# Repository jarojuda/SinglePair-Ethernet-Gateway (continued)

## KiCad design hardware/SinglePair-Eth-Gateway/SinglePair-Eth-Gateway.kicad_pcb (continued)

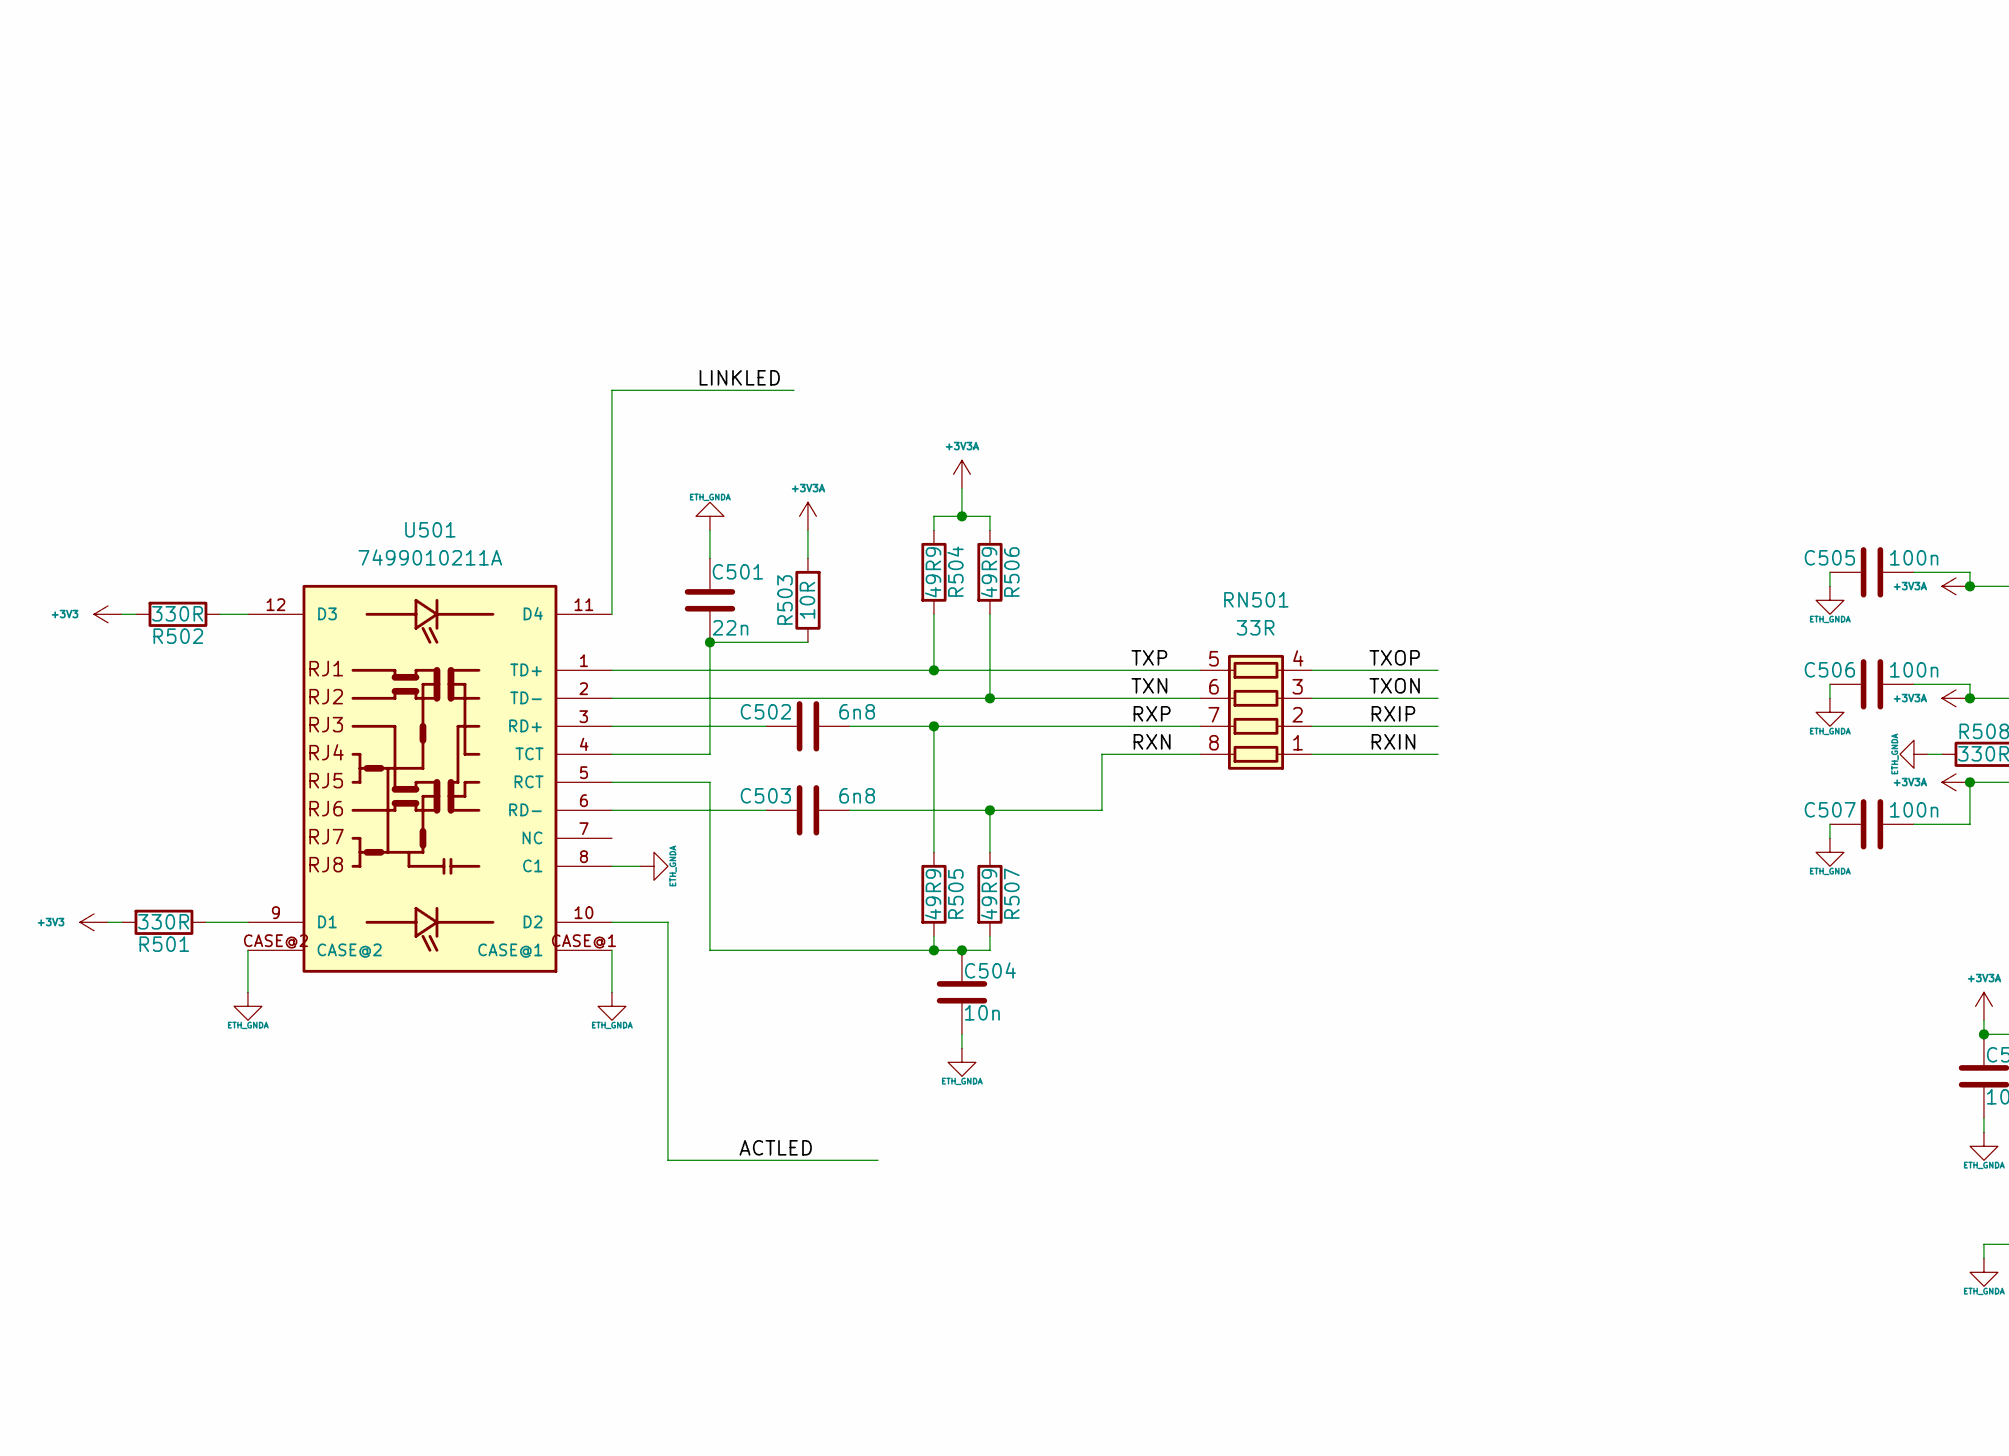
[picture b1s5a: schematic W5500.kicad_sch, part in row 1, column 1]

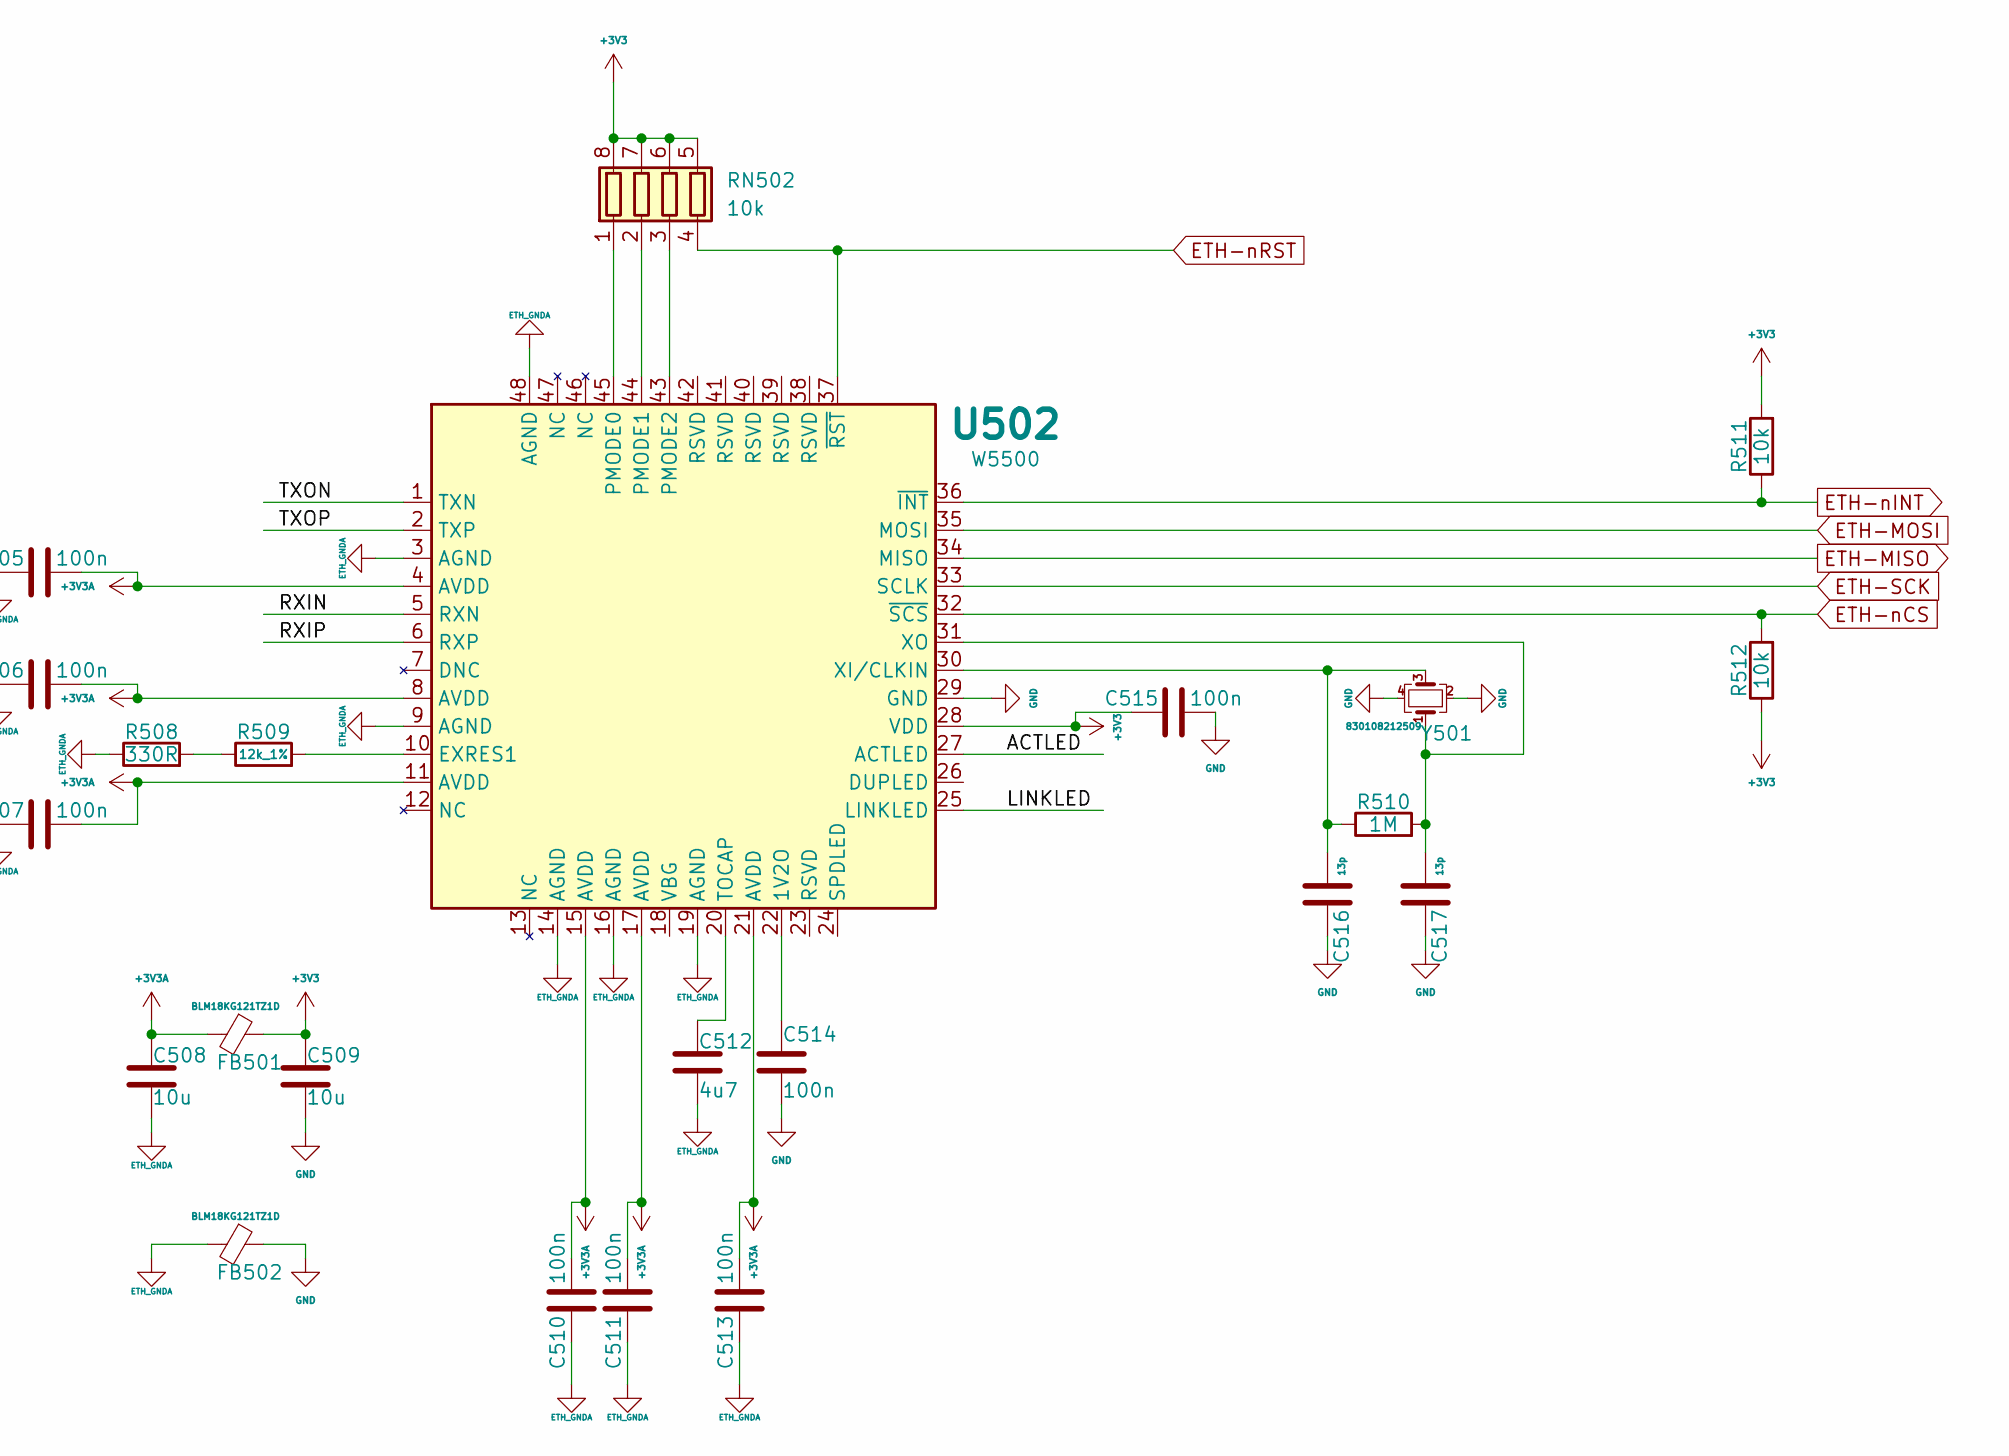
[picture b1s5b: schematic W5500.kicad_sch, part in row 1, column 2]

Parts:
C501: 22n; C_0603_1608Metric
C502, C503: 6n8; C_0603_1608Metric
C504: 10n; C_0603_1608Metric
C505, C506, C507, C510, C511, C513, C514, C515: 100n; C_0603_1608Metric
C508, C509: 10u; C_0805_2012Metric
C512: 4u7; C_0603_1608Metric
C516, C517: 13p; C_0603_1608Metric
FB501, FB502: BLM18KG121TZ1D; FB_0603_1608Metric
R501, R502, R508: 330R; R_0603_1608Metric
R503: 10R; R_0603_1608Metric
R504, R505, R506, R507: 49R9; R_0603_1608Metric
R509: 12k_1%; R_0603_1608Metric
R510: 1M; R_0603_1608Metric
R511, R512: 10k; R_0603_1608Metric
RN501: 33R; R_Array_Concave_4x0603
RN502: 10k; R_Array_Concave_4x0603
U501: 7499010211A
U502: W5500; LQFP-48_7x7mm_P0.5mm
Y501: 830108212509; Crystal_SMD_2016-4Pin_2.0x1.6mm

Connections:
+3V3: C509.1, C515.1, FB501.1, R501.2, R502.2, R511.2, R512.1, RN502.5 (R4.2), RN502.6 (R3.2), RN502.7 (R2.2), RN502.8 (R1.2), U502.28 (VDD); also elsewhere on the board
+3V3A: C505.2, C506.2, C507.2, C508.1, C510.2, C511.2, C513.2, FB501.2, R503.2, R504.1, R506.1, U502.4 (AVDD), U502.8 (AVDD), U502.11 (AVDD), U502.15 (AVDD), U502.17 (AVDD), U502.21 (AVDD)
/Wiznet-W5500/ACTLED: U501.10 (D2), U502.27 (ACTLED)
/Wiznet-W5500/LINKLED: U501.11 (D4), U502.25 (LINKLED)
/Wiznet-W5500/RXIN: RN501.1 (R1.1), U502.5 (RXN)
/Wiznet-W5500/RXIP: RN501.2 (R2.1), U502.6 (RXP)
/Wiznet-W5500/RXN: C503.2, R507.1, RN501.8 (R1.2)
/Wiznet-W5500/RXP: C502.2, R505.1, RN501.7 (R2.2)
/Wiznet-W5500/TXN: R506.2, RN501.6 (R3.2), U501.2 (TD-)
/Wiznet-W5500/TXON: RN501.3 (R3.1), U502.1 (TXN)
/Wiznet-W5500/TXOP: RN501.4 (R4.1), U502.2 (TXP)
/Wiznet-W5500/TXP: R504.2, RN501.5 (R4.2), U501.1 (TD+)
ETH-MISO: U502.34 (MISO); also elsewhere on the board
ETH-MOSI: U502.35 (MOSI); also elsewhere on the board
ETH-SCK: U502.33 (SCLK); also elsewhere on the board
ETH-nCS: R512.2, U502.32 (~SCS); also elsewhere on the board
ETH-nINT: R511.1, U502.36 (~INT); also elsewhere on the board
ETH-nRST: RN502.4 (R4.1), U502.37 (~RST); also elsewhere on the board
ETHGNDA: C501.2, C504.2, C505.1, C506.1, C507.1, C508.2, C510.1, C511.1, C512.2, C513.1, FB502.2, R508.1, U501.8 (C1), U501.CASE@1, U501.CASE@2, U502.3 (AGND), U502.9 (AGND), U502.14 (AGND), U502.16 (AGND), U502.19 (AGND), U502.48 (AGND)
GND: C509.2, C514.2, C515.2, C516.1, C517.2, FB502.1, U502.29 (GND), Y501.2, Y501.4; also elsewhere on the board
unnamed: R508.2, R509.1
unnamed: RN502.1 (R1.1), U502.45 (PMODE0)
unnamed: RN502.2 (R2.1), U502.44 (PMODE1)
unnamed: RN502.3 (R3.1), U502.43 (PMODE2)
unnamed: R501.1, U501.9 (D1)
unnamed: R502.1, U501.12 (D3)
unnamed: C504.1, R505.2, R507.2, U501.5 (RCT)
unnamed: C502.1, U501.3 (RD+)
unnamed: C503.1, U501.6 (RD-)
unnamed: C501.1, R503.1, U501.4 (TCT)
unnamed: C514.1, U502.22 (1V2O)
unnamed: R509.2, U502.10 (EXRES1)
unnamed: C512.1, U502.20 (TOCAP)
unnamed: C516.2, R510.1, U502.30 (XI/CLKIN), Y501.3
unnamed: C517.1, R510.2, U502.31 (XO), Y501.1

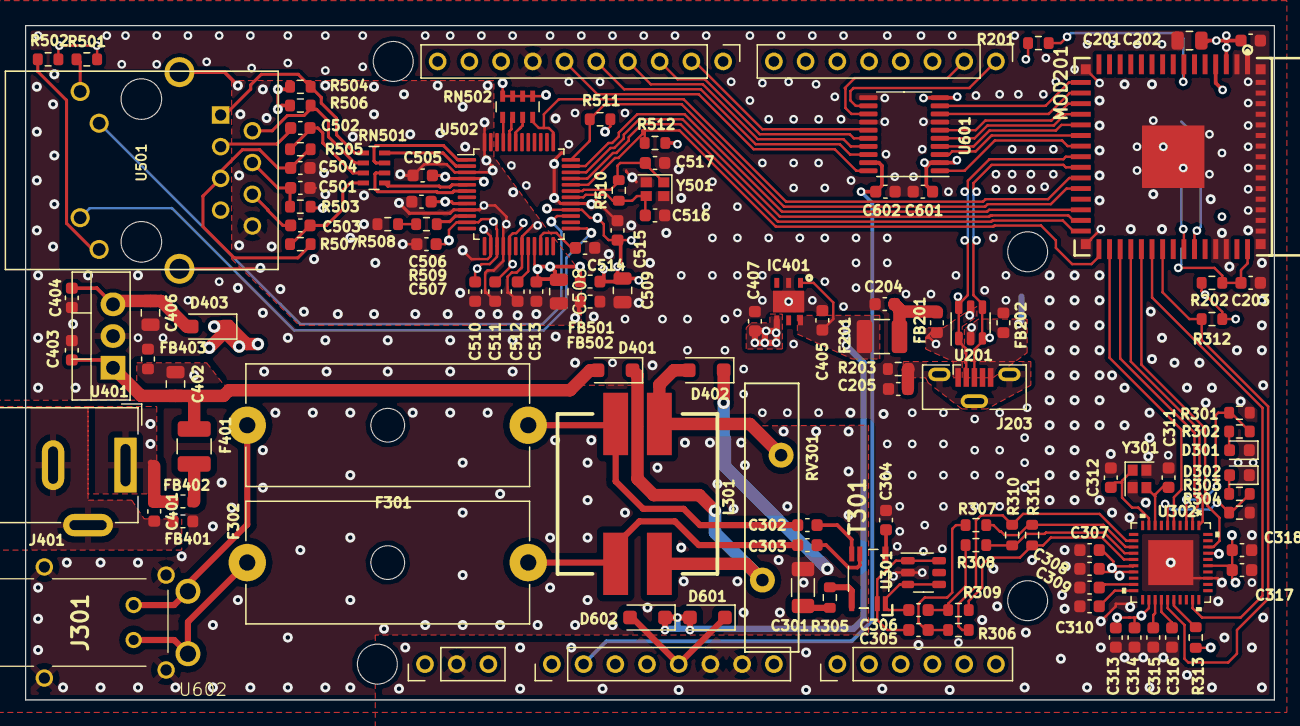
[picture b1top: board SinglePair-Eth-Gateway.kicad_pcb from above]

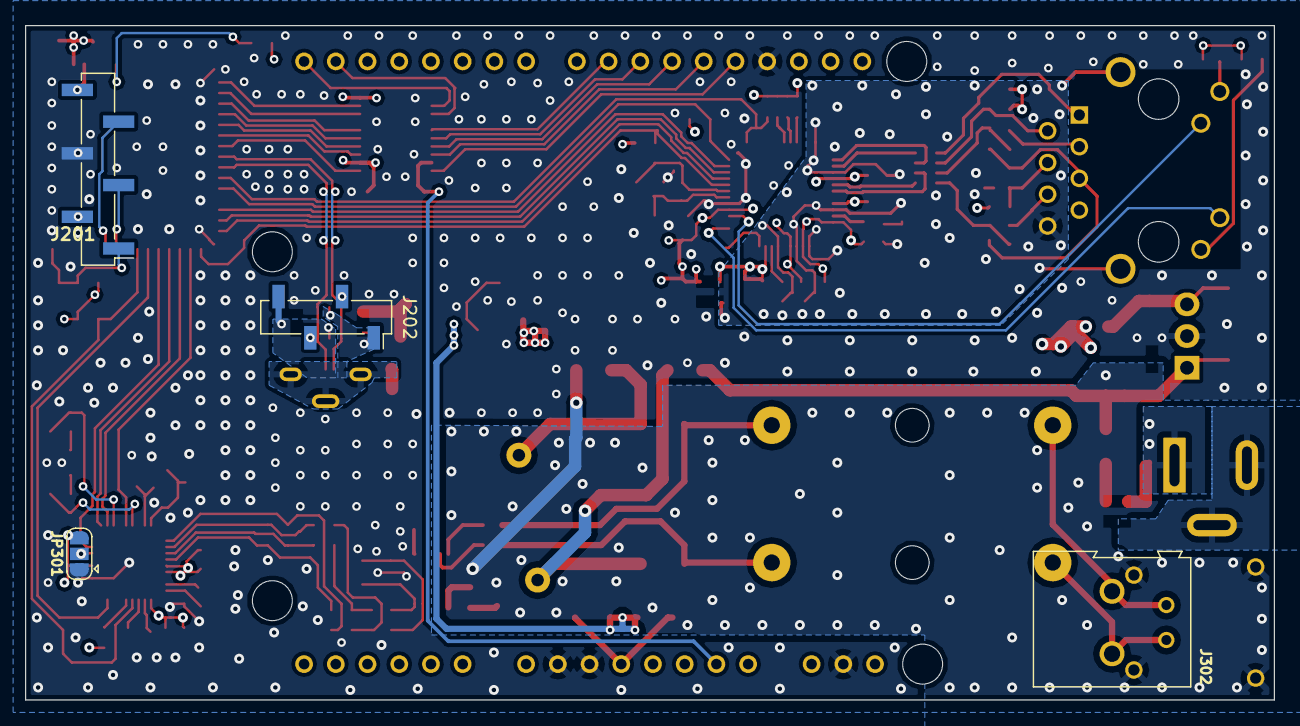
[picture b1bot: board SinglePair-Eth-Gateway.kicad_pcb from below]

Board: 4 copper layers, 100.0 x 54.0 mm, 119 parts (4 on the bottom side), 106 nets.

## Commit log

2024-01-01 First prototype
2024-01-26 Change position of values on the Fab layer
